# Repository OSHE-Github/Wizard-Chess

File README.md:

# Wizard-Chess

Wizaard Chess is an open source project that aims to have a physical chessboard that can record the pieces, positions, and movements of a chess game. This project combines the experience of playing on a physical chessboard with the advantages of a digital chess game!

Using shift registers, hall effect sensors, and magnets Wizard Chess senses where pieces are on the squares and records that information. Using other open source chess libraries the board is able to detect and record moves. When an illegal move is made the board alerts the player on the display screens. Display screens also display a clock that players can adjust the time limit of as well as stop and start with buttons on their side of the board. 

# Repository Navigation:
First navigate to the Project Materials & Instructions. This will show the bill of materials for the project. Listed in it is all if the parts that were used in the project, as well as the amount needed for each part, the cost, and link to purchase the part for yourself! Also under this section will be the Assembly Documentation.  To find the CAD files navigate to the Chessboard CAD folder. In there will be a file called LinkToCAD.txt. The link in the document will take you to an onshape file that can be copied. This file contains the full CAD for the project! Next, find the Chess Board KiCAD. This is the schematic for the board and will tell you how the electronics are supposed to be connected. Once you are ready for testing, there are files for tetsting the shift registers on their own, testing the shift registers with the hall effect sensors, and testing the chess library.

# Note:
This project references another open source chess project OpenChess. Feel free to go check it out: https://github.com/joojoooo/OpenChess
Along with that we also reference the OLED Library http://rinkydinkelectronics.com/library.php?id=79 , and the Chess Library https://github.com/codewitch-honey-crisis/htcw_chess

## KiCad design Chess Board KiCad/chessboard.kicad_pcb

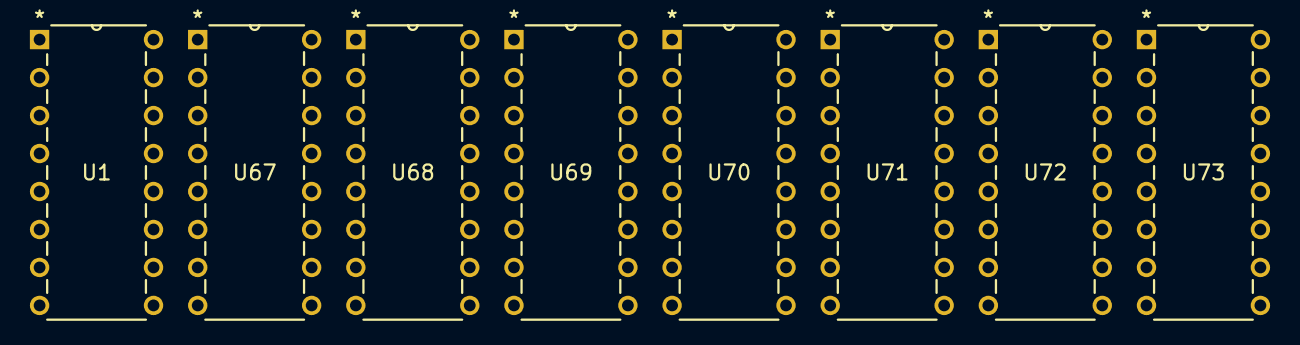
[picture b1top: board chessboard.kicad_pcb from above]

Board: 2 copper layers, 8 parts (0 on the bottom side), 12 nets, no tracks yet.

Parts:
U1, U67, U68, U69, U70, U71, U72, U73: SN74HC165N; N16

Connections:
/shift-registers/CLK: U1.2 (CLK), U67.2 (CLK), U68.2 (CLK), U69.2 (CLK), U70.2 (CLK), U71.2 (CLK), U72.2 (CLK), U73.2 (CLK)
/shift-registers/CLK INH: U1.15 (CLKINH), U67.15 (CLKINH), U68.15 (CLKINH), U69.15 (CLKINH), U70.15 (CLKINH), U71.15 (CLKINH), U72.15 (CLKINH), U73.15 (CLKINH)
/shift-registers/GND: U1.8 (GND), U67.8 (GND), U68.8 (GND), U69.8 (GND), U70.8 (GND), U71.8 (GND), U72.8 (GND), U73.8 (GND)
/shift-registers/LOAD: U1.1 (SH/*LD), U67.1 (SH/*LD), U68.1 (SH/*LD), U69.1 (SH/*LD), U70.1 (SH/*LD), U71.1 (SH/*LD), U72.1 (SH/*LD), U73.1 (SH/*LD)
/shift-registers/VCC: U1.16 (VCC), U67.16 (VCC), U68.16 (VCC), U69.16 (VCC), U70.16 (VCC), U71.16 (VCC), U72.16 (VCC), U73.16 (VCC)
unnamed: U1.9 (QH), U67.10 (SER)
unnamed: U67.9 (QH), U68.10 (SER)
unnamed: U68.9 (QH), U69.10 (SER)
unnamed: U69.9 (QH), U70.10 (SER)
unnamed: U70.9 (QH), U71.10 (SER)
unnamed: U71.9 (QH), U72.10 (SER)
unnamed: U72.9 (QH), U73.10 (SER)
